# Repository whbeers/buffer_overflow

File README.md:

# Buffer Overflow Drive Effect

This is a re-creation of the DOD Overdrive 250 / MXR Distortion+ op-amp drive circuit, as a first attempt at basic PCB design in [KiCAD](https://www.kicad.org/). 

The board is built on the ["Noise Floor"](https://github.com/whbeers/noise_floor) pedal platform, which provides basic power protection, audio IO, and a footswitch with LED indicator.

[Schematic PDF](schematics/buffer_overflow-latest.pdf)

## Credit
The basic schematic I worked from is available from a variety of sources, but this was primarily derived from the [PedalPCB Distortion 250](https://www.pedalpcb.com/product/dist250/). I strongly endorse PedalPCB (and this pedal) as a great way to get started building effects.

Thanks as always to the folks on the [freestompboxes.org](https://www.freestompboxes.org/) forum for feedback and suggestions.

Conan Lite footprints adapted from the 51-position footprints available from SnapEDA: [Header](https://www.snapeda.com/parts/10162582-1134151LF/Amphenol%20ICC%20(FCI)/view-part/), [Receptacle](https://www.snapeda.com/parts/10162581-3134151LF/Amphenol%20ICC%20(FCI)/view-part/).([Additional license details](hardware/SnapEDA_Licensing.txt)). 3D models courtesy Amphenol.

*I am not affiliated with any of the brands, sites, or products named in this overview.*

## Versioning

My pcb designs utilize the following versioning scheme (I'll add to this as I produce more revisions):
 - v0.0XX: A candidate design that has not yet been produced and tested.
 - v0.XX: A design that has been produced, tested, and any initial errors addressed.

## Note on v0.40

v0.40 updates Buffer Overflow as a proof-of-concept for the experimental [Noise Floor](https://github.com/whbeers/noise_floor) UX board, which uses board-to-board connectors to modularize the control surface the effect. While it only exercises two potentiometers from the UX board, I may expand use of it (e.g. switchable clipping diode banks, etc).

I've also changed resistors and capacitors to 1206 SMD parts. Due to the fact that the board-to-board assemblies are also surface mount, it meant moving almost all parts to the back of the board. This resulted in an awkward-looking layout, to say the least, and I expect it to evolve over time.

## Name
*The name "Buffer Overflow" is a reflection of the nature of the effect (an overdrive) and security nerdery.*

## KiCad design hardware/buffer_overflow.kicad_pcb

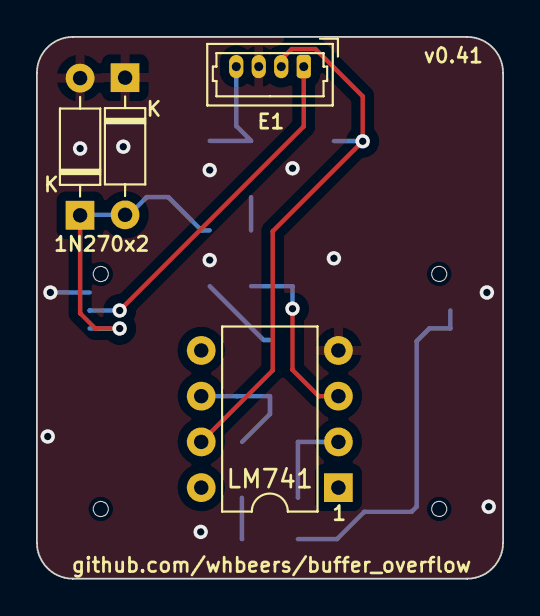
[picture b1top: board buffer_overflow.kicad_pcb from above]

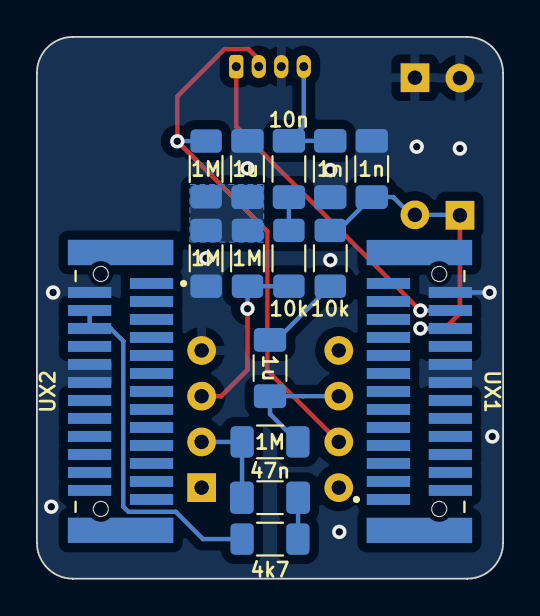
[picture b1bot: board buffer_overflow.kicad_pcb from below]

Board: 2 copper layers, 25.9 x 30.1 mm, 19 parts (15 on the bottom side), 13 nets.

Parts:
C1, C7: 1n; C_1206_3216Metric_Pad1.33x1.80mm_HandSolder
C3: 10n; C_1206_3216Metric_Pad1.33x1.80mm_HandSolder
C4: 47n; C_1206_3216Metric_Pad1.33x1.80mm_HandSolder
C5, C6: 1u; C_1206_3216Metric_Pad1.33x1.80mm_HandSolder
D3, D4: 1N270; D_DO-35_SOD27_P7.62mm_Horizontal
J1: E1; Molex_PicoBlade_53047-0410_1x04_P1.25mm_Vertical_with_3D_Mo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
J2: UX1; Amphenol_Header_25Pin_10162582-1134125LF
J3: UX2; Amphenol_Header_25Pin_10162582-1134125LF
R2, R8: 10k; R_1206_3216Metric_Pad1.30x1.75mm_HandSolder
R3, R4, R5, R7: 1M; R_1206_3216Metric_Pad1.30x1.75mm_HandSolder
R6: 4k7; R_1206_3216Metric_Pad1.30x1.75mm_HandSolder
U1: LM741; DIP-8_W7.62mm

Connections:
/9V0: J1.2, R4.2, U1.7 (V+)
/741_Inv: C4.2, R7.2, U1.2 (-)
/741_NonInv: R2.2, R3.1, U1.3 (+)
/741_OUT: C6.1, R7.1, U1.6
/EFFECT_IN: C1.2, C3.1, J1.4
/EFFECT_OUT: J1.1, J2.24
/GAIN_CTL: J3.15, J3.16, R6.2
/POT3_CW: C7.2, D3.2 (A), D4.1 (K), J2.23, R8.1
/VREF: C5.1, R3.2, R4.1, R5.2
GND: C1.1, C5.2, C7.1, D3.1 (K), D4.2 (A), J1.3, J2.20, J2.21, J2.25, J3.14, J3.18, J3.19, R5.1, U1.4 (V-)
unnamed: C3.2, R2.1
unnamed: C4.1, R6.1
unnamed: C6.2, R8.2

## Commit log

2023-02-15 add a non-lame schematic PDF
2023-02-15 todo on bom
2023-02-21 Fix issues identified in v0.01
    Bugfixes:
    - Reverse swapped opamp inputs
    - Reverse backwards Volume potentiometer
    Enhancements:
    - Cosmetic and functional updates to silkscreen
    - Include revision and github reference
2023-02-21 Updated renders
2023-02-22 Update README.md
    add versioning notes
2023-02-22 fix alignment of potentiometers
2023-02-22 Mostly cosmetic updates
    - replace LED footprint with 3mm non-flat
    - shift text around
    - fix grid alignment for edge cuts
    - misc text updates
2023-02-22 add back surface finish
2023-02-24 Change to CC0 license
2023-02-28 Address issues found in v0.1 hardware
    - cosmetic and usability changes
2023-03-01 Updates for v0.30: - Replace wire connections with molex picoblade connectors - Many cosmetic changes and layout changes to reduce size and improve appearance
2023-03-01 Update README.md
    Eliminate claims that this is compatible with PedalPCB 3PDT adapters, now that I've switched to picoblade connectors.
2023-03-02 update gitignore to include library and symbol tables
2023-03-02 add symbol table
2023-03-03 Offload functions of "noise floor" interface boards for v0.35
    - more layout changes coming, but functionality should be the same.
2023-03-03 condense and optimize layout
2023-03-03 swap connectors to be on the same side as Noise Floor
2023-03-03 condense to a single connector, bump rev to v0.38
2023-03-03 update schematic with correct identifier for E1
2023-03-04 Some updates based on feedback from freestompboxes.org folks:
    - Add back thermal reliefs on ground pads
    - Switch to stereo jacks for improved mechanical support
    - Add 3D models for various parts (courtesy of Vasily Kashirin - https://grabcad.com/vasily.kashirin-1/models?page=1)
    - Add more space between potentiometers (need to update the courtyard to make this more obvious in the future)
2023-03-04 fix a couple DRCs
2023-03-05 add script to generate schematic, saving time at release. also embed an SVG schematic in README.
2023-03-05 remove version note from README
2023-03-05 add script to export gerbers and drill files
2023-03-10 update schematic plotting script to create the directory if it doesn't exist
2023-03-10 generate new schematic (although nothing should have updated)
2023-03-13 Update to latest stable kicad version:
    - fixed issue rendering certain 3d models in color
    - had to fix some text rendering changes
2023-03-13 update renders.
2023-03-16 no-op changes
2023-03-17 add disclaimer
2023-03-27 make readme consistent with others
2023-03-28 v0.40 - proof-of-concept for Noise Floor UX board
    - change to SMD resistors and capacitors
    - full re-layout and re-route to accomodate board-to-board assemblies
2023-03-28 Update readme with note about snapeda part licensing, remove potentiometers
2023-04-17 Fix issue detected in hardware version v0.40
    - swap backwards volume knob pins
2023-04-17 update schematic
